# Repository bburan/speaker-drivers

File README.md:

# Speaker drivers (2 watt)

## Overview

This circuit can drive a small earphone speaker that requires up to 2 watts of power (e.g., 500 mA current into an 8 ohm speaker). 

* It has unity gain in a non-inverting configuration (the speakers we work with only require about 1V maximum to achieve the desired sound levels).
* High-pass input stage with 1.26 Hz cutoff (basically a DC filter).
* Two BUF634 in parallel to provide up to 500 mA of current.

The board is 74mm x 48mm and the mounting holes, spaced 40mm x 40mm, are sized for a M3 screw. The board will fit in a Hammond enclosure that accomodates 75mm wide boards.

## Getting started

OSH Park will print and ship three of these boards for approximately $30. 

Order the parts from the [parts list](speaker%20drivers%20part%20list.md). If you get a heat sink, Aavid Thermalloy 577202B00000G should fit nicely in the space allowed.

Solder all components. Be sure to attach heat sinks to the current buffers.

Wash the board with dH<sub>2</sub>O.

## Notes

Previous iterations of the design had a high-pass filter on the output.  However, we have modified the current iteration such that the high-pass filter is found on the input stage. This allows us to eliminate bulky components (required to handle the large current) that take up a lot of space.

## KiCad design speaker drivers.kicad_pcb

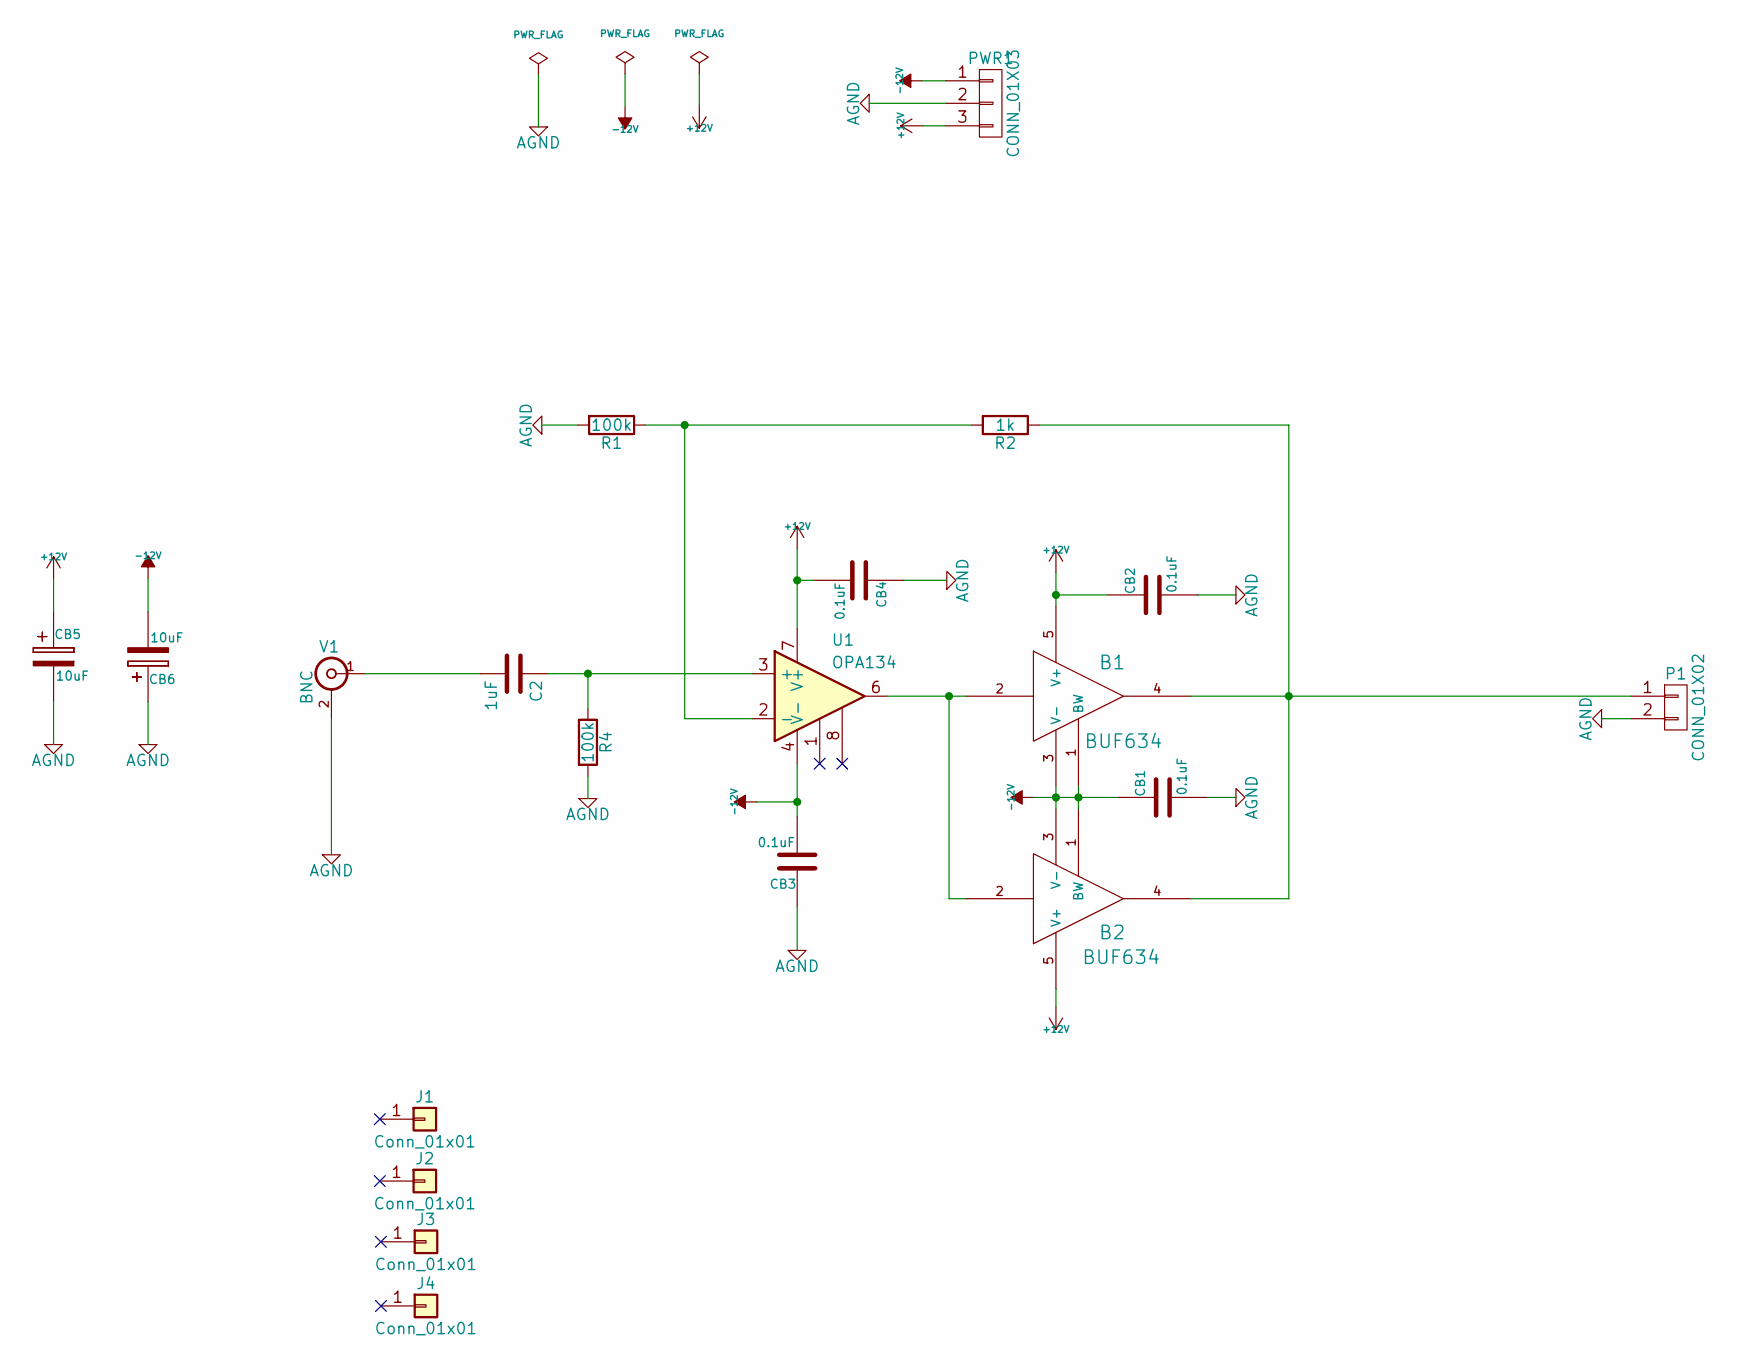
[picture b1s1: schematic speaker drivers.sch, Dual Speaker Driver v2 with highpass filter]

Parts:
B1, B2: BUF634; TO-220-5_Vertical
C2: 1uF; CP_Radial_D5.0mm_P2.50mm
CB1, CB2, CB3, CB4: 0.1uF; C_Rect_L4.0mm_W3.5mm_P2.50mm
CB5, CB6: 10uF; CP_Radial_D5.0mm_P2.50mm
J1, J2, J3, J4: Conn_01x01; MountingHole_3.2mm_M3
P1: CONN_01X02; PinHeader_1x02_P2.54mm_Vertical
PWR1: CONN_01X03; PinHeader_1x03_P2.54mm_Vertical
R1, R4: 100k; R_Axial_DIN0207_L6.3mm_D2.5mm_P7.62mm_Horizontal
R2: 1k; R_Axial_DIN0207_L6.3mm_D2.5mm_P7.62mm_Horizontal
U1: OPA134; DIP-8_W7.62mm_LongPads
V1: BNC; Socket_Strip_Straight_1x02

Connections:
+12V: B1.5 (V+), B2.5 (V+), CB2.1, CB4.2, CB5.1, PWR1.3, U1.7 (V+)
-12V: B1.1 (BW), B1.3 (V-), B2.1 (BW), B2.3 (V-), CB1.1, CB3.2, CB6.2, PWR1.1, U1.4 (V-)
AGND: CB1.2, CB2.2, CB3.1, CB4.1, CB5.2, CB6.1, P1.2, PWR1.2, R1.2, R4.2, V1.2 (Ext)
unnamed: B1.2, B2.2, U1.6
unnamed: B1.4, B2.4, P1.1, R2.1
unnamed: C2.1, R4.1, U1.3 (+)
unnamed: C2.2, V1.1 (In)
unnamed: R1.1, R2.2, U1.2 (-)

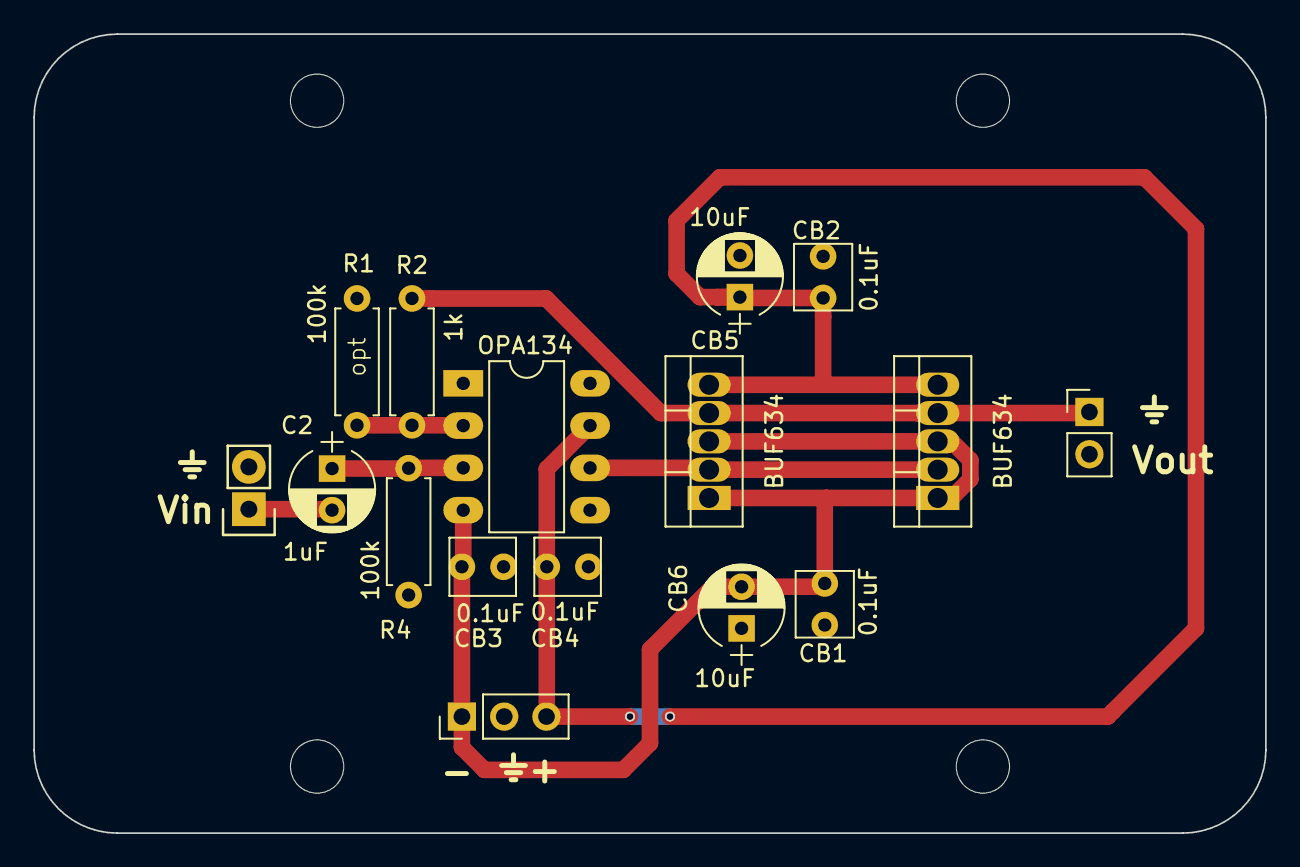
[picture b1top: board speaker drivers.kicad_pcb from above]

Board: 2 copper layers, 74.0 x 48.0 mm, 20 parts (0 on the bottom side), 8 nets.

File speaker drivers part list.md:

| References         | Number | Value         | Part number        | Note                  |
| ------------------ | ------ | ------------- | ------------------ | --------------------- |
| B1, B2             | 2      | BUF634        | BUF634T            | heat sink recommended |
| C2                 | 1      | 1uF           | MKS02-1/50/10      | metal film            |
| CB1, CB2, CB3, CB4 | 4      | 0.1uF         | RDER72A104K1S1H03A |                       |
| CB5, CB6           | 2      | 10uF          | TAP106M025SCS      | tantalum recommended  |
| J1, J2, J3, J4     | 4      | mounting hole |                    |                       |
| P1                 | 1      | 0.1" header   |                    |                       |
| P2                 | 1      | 0.1" header   |                    |                       |
| P3                 | 1      | 0.1" header   |                    |                       |
| R1, R4             | 2      | 100k          | YR1B100KCC         |                       |
| R2                 | 1      | 1k            | YR1B1K0CC          |                       |
| U1                 | 1      | OPA134        | OPA134PA           |                       |

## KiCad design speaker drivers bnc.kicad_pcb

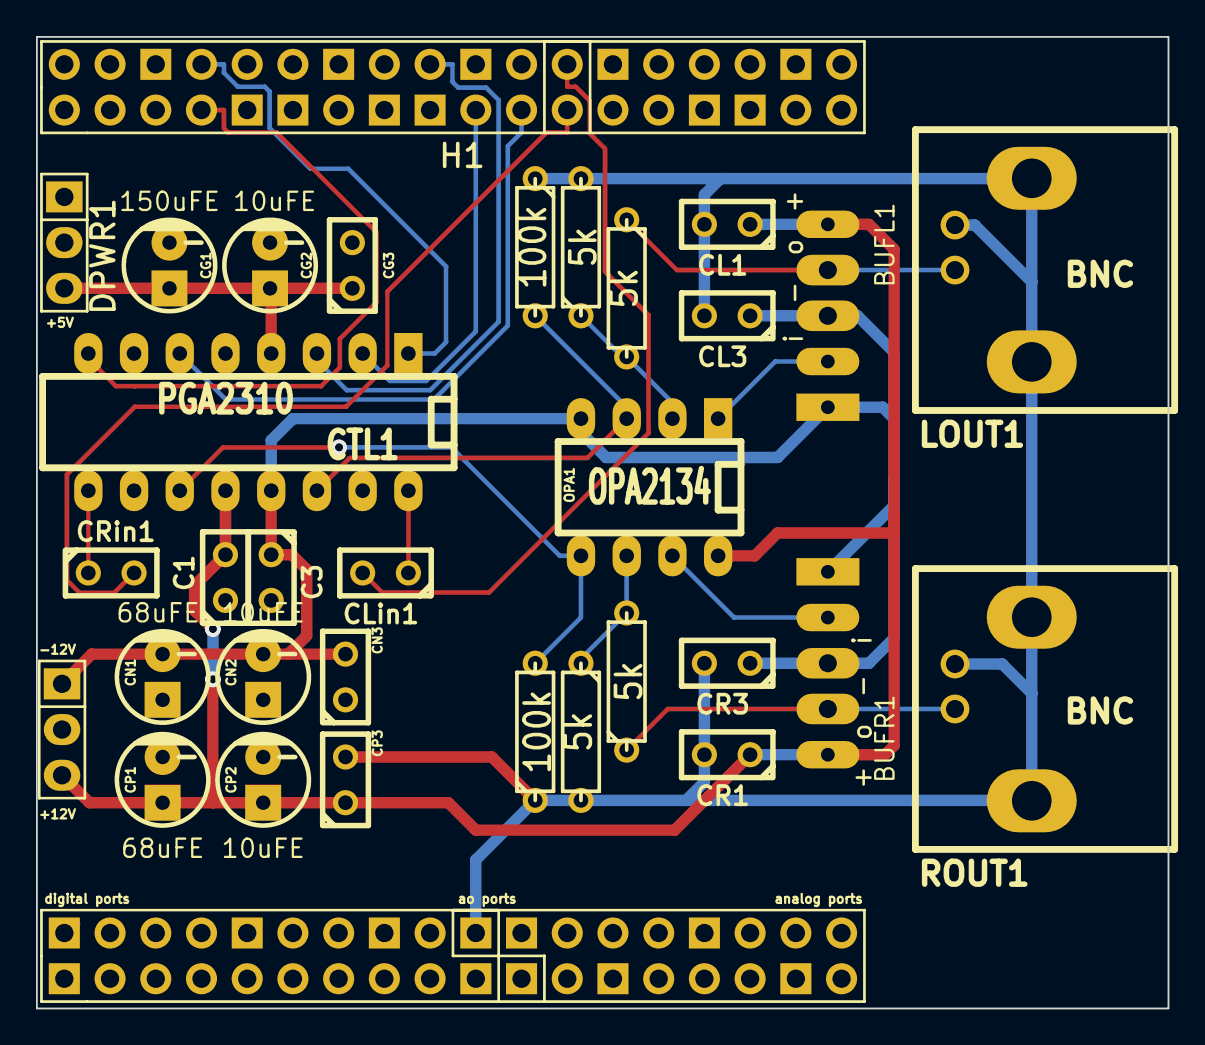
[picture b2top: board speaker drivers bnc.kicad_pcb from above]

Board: 2 copper layers, 62.9 x 54.0 mm, 32 parts (0 on the bottom side), 22 nets.

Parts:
APWR1: CONN_01X03; Socket_Strip_Straight_1x03
BUFL1: BUF634
BUFR1: BUF634
C1, C3: 0.1uFC; C1
CG1: 150uFE; Capacitor5x6RM2.5
CG2: 10uFE; Capacitor5x6RM2.5
CG3: 0.1uFC; C1
CL1, CL3: 10uFT; C1
CLin1: 1uF; C1
CN1: 68uFE; Capacitor5x6RM2.5
CN2: 10uFE; Capacitor5x6RM2.5
CN3: 0.1uFC; C1
CP1: 68uFE; Capacitor5x6RM2.5
CP2: 10uFE; Capacitor5x6RM2.5
CP3: 0.1uFC; C1
CR1, CR3: 10uFT; C1
CRin1: 1uF; C1
CTL1: PGA2310; DIP-16__300_ELL
DPWR1: CONN_01X03; Socket_Strip_Straight_1x03
H1: NI_header; 2x2x18
LOUT1: BNC; BNC_Socket_TYCO-AMP_RevA_Date21Jun2010
OPA1: OPA2134; DIP-8__300_ELL
RL1, RL2: 5k; R3
RL3: 100k; R3
ROUT1: BNC; BNC_Socket_TYCO-AMP_RevA_Date21Jun2010
RR1, RR2: 5k; R3
RR3: 100k; R3

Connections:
+5V: CG1.1, CG2.1, CG3.1, CTL1.4, DPWR1.3
+12V: APWR1.3, BUFL1.5, BUFR1.5, C1.2, CL1.1, CP1.1, CP2.1, CP3.1, CR1.1, CTL1.12, OPA1.8
-12V: APWR1.1, BUFL1.1, BUFL1.3, BUFR1.1, BUFR1.3, C3.1, CL3.1, CN1.2, CN2.2, CN3.2, CR3.1, CTL1.13, OPA1.4
/CS: CTL1.2, H1.17
/MUTE: CTL1.8, H1.5
/SCLK: CTL1.6, H1.19
/SDI: CTL1.3, H1.16
/ZCEN: CTL1.1, H1.6
AGND: APWR1.2, C1.1, C3.2, CL1.2, CL3.2, CN1.1, CN2.1, CN3.1, CP1.2, CP2.2, CP3.2, CR1.2, CR3.2, CTL1.10, CTL1.15, H1.54, LOUT1.2, RL1.2, RL3.1, ROUT1.2, RR1.2, RR3.1
DGND: CG1.2, CG2.2, CG3.2, CTL1.5, DPWR1.2
unnamed: BUFL1.2, OPA1.1
unnamed: BUFL1.4, LOUT1.1, RL2.1
unnamed: BUFR1.2, OPA1.7
unnamed: BUFR1.4, ROUT1.1, RR2.1
unnamed: CLin1.1, CTL1.16
unnamed: CLin1.2, H1.22
unnamed: CRin1.1, CTL1.9
unnamed: CRin1.2, H1.21
unnamed: CTL1.11, OPA1.5, RR3.2
unnamed: CTL1.14, OPA1.3, RL3.2
unnamed: OPA1.2, RL1.1, RL2.2
unnamed: OPA1.6, RR1.1, RR2.2

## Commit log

2014-10-07 Initial commit of circuits for LBHB
2014-10-07 Speaker drivers V1 ready for fabrication
2014-10-07 BNC version of speaker driver V1
2014-10-07 Fixes to speaker driver circuit
    * Ensure bypass caps between -12V and GND are correct orientation
    * Add notation for all caps indicating size
    * Widen drill holes in BUF634
    * Ensure cap symbols show orientation when needed
2014-10-09 Connect P0.0 to PFI0 ... PFI2 in speaker drivers circuit
2015-01-07 Commit before modifying speaker driver schematic
2015-02-17 ENH: Working draft of speaker drivers v2
2015-02-17 CLN: Cleanup of speaker drivers folder
2015-02-17 CLN: Don't track gerber folders
2015-11-20 Commit before major revisions
2015-11-30 WIP: Preliminary commit before splitting boards
2015-12-15 WIP: Test of new circuit for speaker drivers
    Note that this circuit does not work and should not be used for
    production.
2015-12-18 ENH: Revisions to speaker drivers
2018-02-01 Fixed bug in previous version and updated design
    * Inverting and noninverting inputs were swapped in the schematic. Fixed
    this bug.
    * Removed the highpass filter that follows the current buffer with a
    highpass filter at the input to the current buffer. Highpass filter
    simply removes DC offset now.
2018-02-06 Added readme
2018-02-06 Fix image of circuit board
2018-02-06 Rename PCB image
2018-02-06 Add information on heat sink

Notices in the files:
speaker drivers.sch:
This is licensed under GPLv3
